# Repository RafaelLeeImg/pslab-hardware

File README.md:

# PSLab Hardware

This is a special branch `diff-img` where the changes made on all four layers relative to the immediate previous board is presented as a diff image.

## Current Layers

<details>
  <summary>External Layers</summary>

| Top | Bottom |
| --- | ------ |
|  |  |
</details>

<details>
  <summary>Internal Layers</summary>

| Power | Signal |
| ----- | ------ |
|  |  |
</details>

## Legend

🟥 what the new board has

🟦 what the previous board had

## Schematic Changes

## Board Changes

| Top Layer |
| ---------- |
|  |

| Bottom Layer |
| --------- |
|  |

| Power Layer |
| ---------- |
|  |

| Signal Layer |
| --------- |
|  |

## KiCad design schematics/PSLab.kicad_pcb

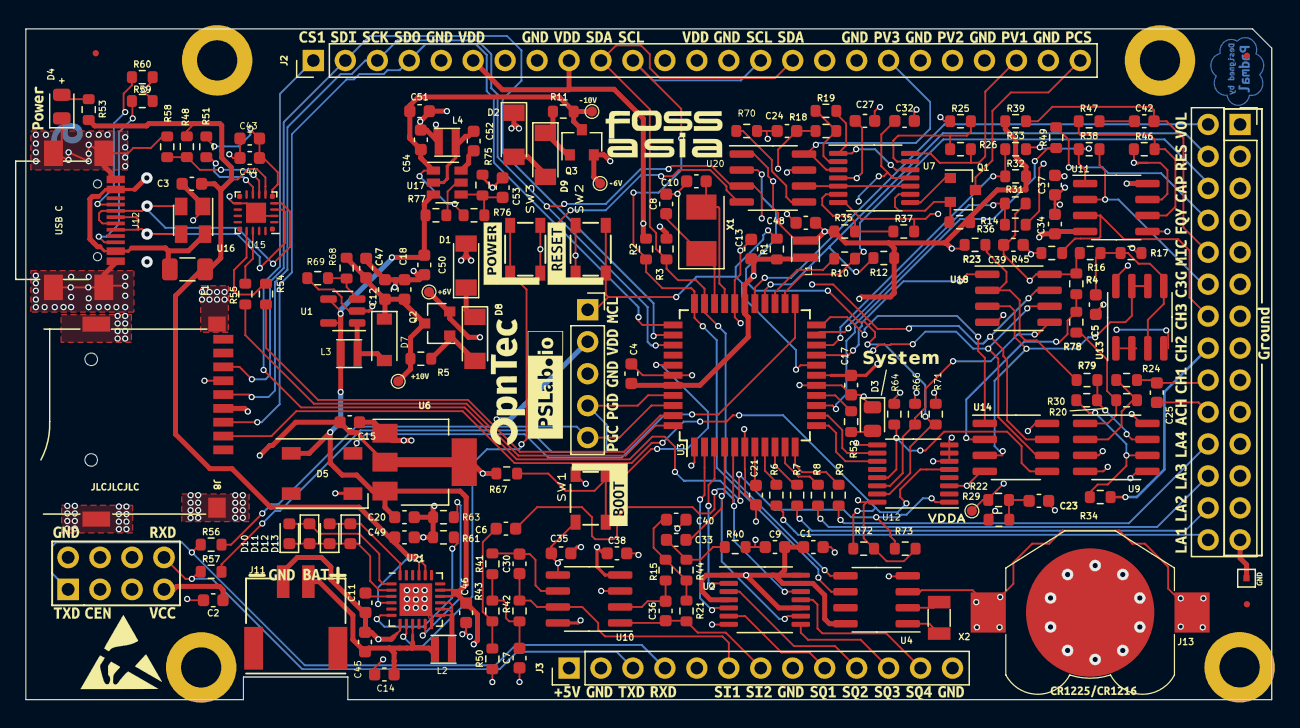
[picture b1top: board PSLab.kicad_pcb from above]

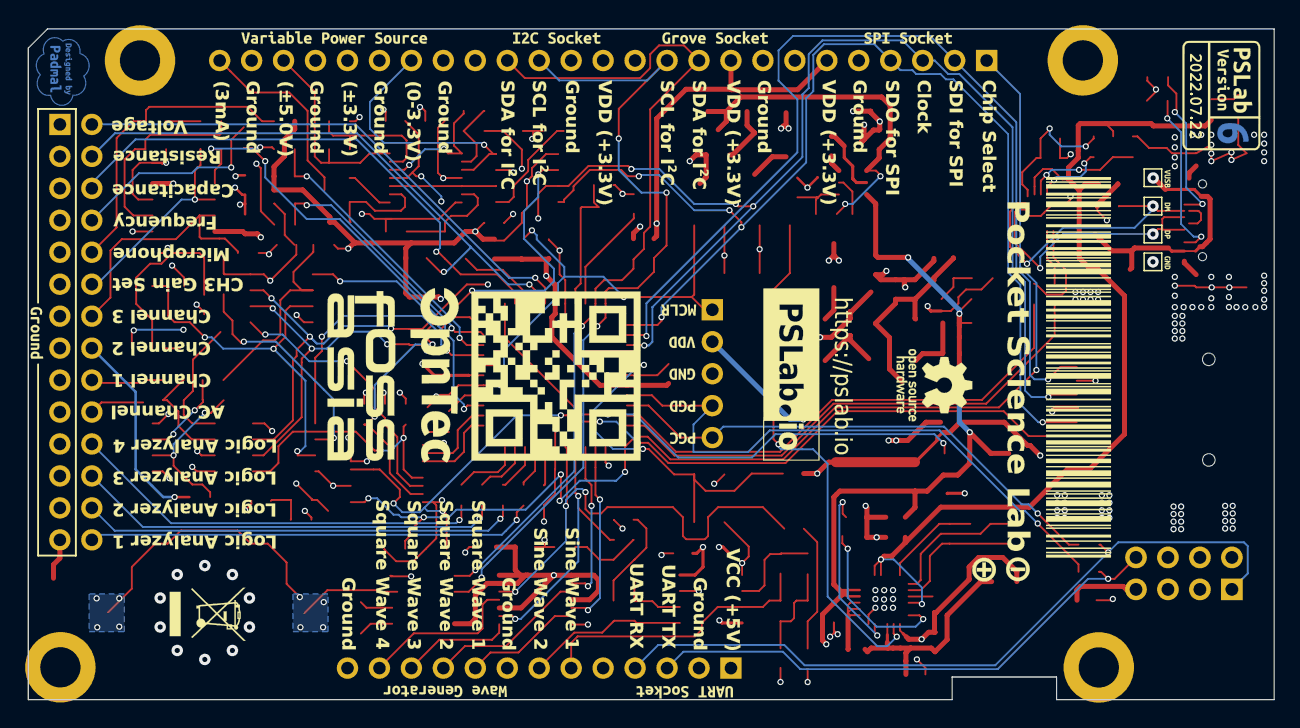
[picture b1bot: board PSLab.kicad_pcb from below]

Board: 4 copper layers, 99.0 x 53.3 mm, 195 parts (8 on the bottom side), 135 nets.

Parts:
C1, C2, C3, C4, C9, C13, C17, C18, C24, C25, C27, C32, C34, C35, C37, C38, C39, C43: 100nF; C_0603_1608Metric
C5, C7, C23, C40: 10nF; C_0603_1608Metric
C6, C12, C14, C15, C21, C33, C44: 10uF; C_0603_1608Metric
C8, C10, C53: 12pF; C_0603_1608Metric
C11: 2.2uF; C_0603_1608Metric
C20, C42, C52: 1uF; C_0603_1608Metric
C30, C36: 1nF; C_0603_1608Metric
C45, C46, C47, C48, C49, C50, C51, C54: 22uF; C_0603_1608Metric
D1, D2: 6.8V; D_MiniMELF
D3: GREEN; LED_0805_2012Metric
D4: BLUE; LED_0805_2012Metric
D5: WS2812B; LED_WS2812B_PLCC4_5.0x5.0mm_P3.2mm
D7: K1N5817HW-7-F; D_SOD-123
D8, D9: 1N4148W; D_MiniMELF
D10, D11, D12, D13: White; LED_0603_1608Metric
F1: 1A; Fuse_1206_3216Metric
FID1, FID2, FID3: Fiducial; Fiducial_0.5mm_Mask1.5mm
J1: DoublePins; PinSocket_2x14_P2.54mm_Vertical
J2: Conn_01x25; PinHeader_1x25_P2.54mm_Vertical
J3: Conn_01x13; PinHeader_1x13_P2.54mm_Vertical
J6: ESP01; ESP-01
J8: Micro_SD_Card_Det_9_pin; TF-015
J10: Programmer; PinSocket_1x05_P2.54mm_Vertical
J11: Battery_Cell; 2.0mm_connector_edge
J12: USB_C - Generic; USB_C_Receptacle_12pin_SMT
J13: CR1225; BatteryHolder_A359
L1, L3, L4: 3.3uH; L_Taiyo-Yuden_MD-2020
L2: 4.7uH; L_Taiyo-Yuden_MD-2020
MH1, MH2, MH3, MH4: M; MountingHole_3.2mm_M3_DIN965_Pad
Q1, Q3: MMBT3906; SOT-23
Q2: MMBT3904; SOT-23
R1, R4, R10, R14, R16, R17, R18, R19, R21, R23, R25, R29, R31, R32, R33, R35, R37, R38, R39, R42, R58, R64, R66, R67, R70, R71, R72, R73, R76, R78, R79: 10k; R_0603_1608Metric
R2, R3, R12, R15, R26, R41, R43, R44, R48, R52, R53, R59, R60: 5.1k; R_0603_1608Metric
R5, R11, R36, R47, R51: 1k; R_0603_1608Metric
R6, R7, R8, R9, R49: 200; R_0603_1608Metric
R20, R30, R40, R46, R50, R63, R77: 200k; R_0603_1608Metric
R22: 12k; R_0603_1608Metric
R24, R34, R45: 1M; R_0603_1608Metric
R54, R55, R56, R57: 18; R_0603_1608Metric
R61: 51k; R_0603_1608Metric
R68: 180k; R_0603_1608Metric
R69: 30k; R_0603_1608Metric
R75: 100k; R_0603_1608Metric
SW1, SW2, SW3: SW_MEC_5E; button_SPST_3x4x2.5
TP1, TP2, TP3, TP5, TP6: TEST; Test_Point_0.8mm
TP4, TP7: GND; TestPoint_Pad_1.0x1.0mm
TP8: VBUS; TestPoint_Pad_1.0x1.0mm
TP9: D-; TestPoint_Pad_1.0x1.0mm
TP10: D+; TestPoint_Pad_1.0x1.0mm
U1: AP3015A; SOT-23-5
U2: 74HC126; TSSOP-14_4.4x5mm_P0.65mm
U3: PIC24EP256GP204; TQFP-44_10x10mm_P0.8mm
U4: DS1307Z+T&R; SOIC-8_3.9x4.9mm_P1.27mm
U6: AMS1117-3.3; SOT-223-3_TabPin2
U7: LM324; TSSOP-14_4.4x5mm_P0.65mm
U9, U10, U11, U13: TL082; SOIC-8_3.9x4.9mm_P1.27mm
U12: 74HC4051; TSSOP-16_4.4x5mm_P0.65mm
U14, U18: MCP6S21-I/SN; SOIC-8_3.9x4.9mm_P1.27mm
U15: CP2102N-xxx-xQFN20x; QFN-20_EP_3x3_Pitch0.5mm
U16: SP0503BAHT; SOT-143
U17: MT1470; SOT-23-6
U20: MCP4822; SOIC-8_3.9x4.9mm_P1.27mm
U21: IP5189T; QFN-24-1EP_4x4mm_P0.5mm_EP2.6x2.6mm
X1: 12MHz; Crystal_SMD_5032-2Pin_5.0x3.2mm
X2: 32.768 kHz; Crystal_SMD_3215-2Pin_3.2x1.5mm
Z1: CR1225; Battery_CR1225
Z6: eWaste; WEEE-Logo_4.2x6mm_SilkScreen
Z7: PSLab BarCode; Barcode
Z8: QR Code; Website_QR
Z9: Val**; Silk
Z10: ESD-Logo; ESD-Logo_6.6x6mm_SilkScreen
Z11: OpenHardware; OSHW-Logo_5.7x6mm_SilkScreen

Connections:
+3V3: C2.1, C4.1, C13.1, C15.2, J2.6, J2.9, J2.13, J6.4 (CH_PD), J6.8 (VCC), J8.4 (VDD), J10.2, L1.2, R1.1, R2.2, R3.2, R64.2, R66.2, R67.2, R71.2, R72.2, R73.2, U3.28 (VDD), U3.40 (VDD), U6.2 (VO), U12.16 (VCC)
+5V: C1.1, C9.1, C20.2, C46.1, C50.1, D5.1 (VDD), J3.1, L3.1, R77.1, U1.4 (EN), U1.5 (VIN), U2.1, U2.4, U2.10, U2.13, U2.14 (VCC), U4.8 (VCC), U6.3 (VI), U17.3 (IN), U21.16 (VOUT), U21.17 (VOUT)
+6V: C27.1, C35.1, C37.1, Q2.2 (E), TP2.1, U7.4 (V+), U9.8 (V+), U10.8 (V+), U11.8 (V+), U13.8 (V+)
+9V: C12.1, C18.1, C47.1, D7.1 (K), Q2.3 (C), R5.2, R68.1, TP6.1
-6V: C32.1, C34.1, C38.1, Q3.2 (E), TP3.1, U7.11 (V-), U9.4 (V-), U10.4 (V-), U11.4 (V-), U13.4 (V-)
-9V: C51.2, C54.2, Q3.3 (C), R11.2, R76.2, TP5.1, U17.1 (GND)
/BAT+: C14.1, C45.1, J11.1 (+), L2.2, U21.9 (VBAT)
/CAP: J1.6, R10.2, U3.24 (PGED1|AN5|C1IN1-|RP35|RB3)
/CC1: J12.A5 (CC1), R60.2
/CC2: J12.B5 (CC2), R59.2
/CP2102_Vreg: C43.1, C44.1, R51.2, U15.6 (VDD)
/D+: J12.A6 (D+), J12.B6 (D+), TP10.1, U15.4 (D+), U16.3 (K)
/D-: J12.A7 (D-), J12.B7 (D-), TP9.1, U15.5 (D-), U16.2 (K)
/DAC.2: U7.5 (+), U7.10 (+), U20.6 (VB)
/LA1_: R6.2, U3.8 (RP42|RB10)
/LA2_: R7.2, U3.9 (RP43|RB11)
/LA3_: R8.2, U3.10 (RPI44|RB12)
/LA4_: R9.2, U3.11 (RPI45|CTPLS|RB13)
/LD1: D12.2 (A), D13.1 (K), U21.24 (L1)
/LD2: D10.2 (A), D11.1 (K), U21.1 (L2)
/LD3: D10.1 (K), D11.2 (A), D12.1 (K), D13.2 (A), U21.2 (L3)
/OSC_IN: C10.1, U3.30 (OSC1|CLKI|RA2), X1.2
/OSC_OUT: C8.1, U3.31 (OSC2|CLKO|RA3), X1.1
/OSC_REF1: U13.6 (-), U13.7, U14.3 (VREF), U18.3 (VREF)
/OSC_REF2: C23.1, R22.1, R29.1
/RES: J1.4, R12.1, U3.26 (AN7|C3IN1-|C4IN1-|RC1)
/RxD: R54.2, U3.43 (RP39|INT0|RB7)
/SQR1_: U2.5, U3.2 (RP54|RC6)
/SQR2_: U2.2, U3.3 (RP55|RC7)
/TxD: R55.2, U3.44 (TCK|ASCL1|RP40|T4CK|RB8)
/VBusSense: R48.2, R58.2, U15.8 (VBUS)
/VINPUT: C3.2, C49.1, F1.2, R48.1, R53.1, U15.7 (VregIn), U21.4 (VTHS), U21.20 (VIN), U21.21 (VIN)
/VOL: J1.2, U3.27 (AN8|C3IN1+|RC2)
/VUSBIN: F1.1, J12.A4 (VBUS), J12.A9 (VBUS), J12.B4 (VBUS), J12.B9 (VBUS), TP8.1, U16.4 (K)
ACH1: C25.2, J1.20
BOOT: R67.1, SW1.1, SW1.2, U3.38 (SCL1|RPI53|RC5)
CH1: C25.1, J1.18, R24.2
CH1_IN: U3.22 (PGEC3|AN3|OA1OUT|RPI33|RB1), U14.1 (OUT)
CH2: J1.16, R34.1
CH2_IN: U3.19 (AN0|OA2OUT|RA0), U18.1 (OUT)
CH3: J1.14, R45.2, U11.3 (+)
CH3.GAIN: J1.12, R38.1, U11.2 (-)
CH3_IN: R32.1, R33.1, U3.20 (AN1|C2IN1+|RA1)
CS1: R64.1, U12.13 (A0), U14.5 (CS)
CS2: R66.1, U12.14 (A1), U18.5 (CS)
CS3: R71.1, U12.15 (A2), U20.2 (~CS)
CS.CH1: U3.12 (TDO|RA10), U12.11 (S0)
CS.CH2: U3.13 (TDI|RA7), U12.10 (S1)
CS.CH3: U3.1 (TMS|ASDA1|RP41|RB9), U12.9 (S2)
FQy: J1.8, R49.2
GND: C1.2, C2.2, C3.1, C4.2, C5.2, C7.2, C8.2, C9.2, C10.2, C11.2, C12.2, C13.2, C14.2, C15.1, C17.2, C18.2, C20.1, C21.2, C23.2, C24.1, C27.2, C32.2, C34.2, C35.2, C37.2, C38.2, C39.2, C40.2, C43.2, C44.2, C45.2, C46.2, C47.2, C48.2, C49.2, C50.2, C51.1, C53.1, C54.1, D1.2 (A), D2.1 (K), D3.1 (K), D4.1 (K), D5.3 (VSS), J1.1, J1.3, J1.5, J1.7, J1.9, J1.11, J1.13, J1.15, J1.17, J1.19, J1.21, J1.23, J1.25, J1.27, J2.5, J2.8, J2.14, J2.18, J2.20, J2.22, J2.24, J3.2, J3.8, J3.13, J6.1 (GND), J8.6 (VSS), J8.10 (SHIELD), J10.3, J11.2 (-), J12.A1 (GND), J12.A12 (GND), J12.B1 (GND), J12.B12 (GND), J12.S1 (SHIELD), J13.2 (-), L4.2, MH1.1, MH2.1, MH3.1, MH4.1, R17.2, R25.1, R29.2, R40.1, R45.1, R50.1, R58.1, R59.1, R60.1, R61.2, R63.2, R69.2, R70.1, R75.1, SW1.3 (K), SW1.4 (A), SW2.3 (K), SW2.4 (A), SW3.1, SW3.2, TP4.1, TP7.1, U1.2 (GND), U2.7 (GND), U3.6 (VSS), U3.16 (GND), U3.29 (VSS), U3.39 (VSS), U4.4 (GND), U6.1 (GND), U9.3 (+), U9.5 (+), U10.3 (+), U10.5 (+), U11.5 (+), U12.3 (A), U12.6 (~E), U12.7 (VEE), U12.8 (GND), U14.4 (GND), U15.3 (GND), U15.12 (GND), U15.21 (GND), U16.1 (A), U18.4 (GND), U20.7 (Vss), U21.7 (AGND), U21.12 (PGND), U21.25 (GND)
LA1: J1.28, R6.1
LA2: J1.26, R7.1
LA3: J1.24, R8.1
LA4: J1.22, R9.1
MCLR: J10.1, R1.2, SW2.1, SW2.2, U3.18 (~MCLR)
MIC: C42.2, J1.10, R39.1
MIC_IN: R14.1, R31.2, U3.21 (PGED3|AN2|C2IN1-|RPI32|RB0)
unnamed: C5.1, R16.1, R17.1, U13.3 (+), U13.5 (+)
unnamed: C6.2, R43.1, R50.2
unnamed: C7.1, R41.1, R42.1, R43.2
unnamed: C11.1, U21.3 (VDD)
unnamed: C21.1, U3.7 (VCAP)
unnamed: C30.2, R41.2, U10.6 (-)
unnamed: C33.2, R40.2, R44.2
unnamed: C36.2, R15.2, U10.2 (-)
unnamed: C40.1, R15.1, R21.1, R44.1
unnamed: C42.1, R47.1
unnamed: C52.1, L4.1, U17.2 (SW)
unnamed: C52.2, U17.6 (BST)
unnamed: C53.2, R75.2, R76.1, U17.4 (FB)
unnamed: D1.1 (K), D8.1 (K)
unnamed: D2.2 (A), D9.2 (A)
unnamed: D3.2 (A), R52.2
unnamed: D4.2 (A), R53.2
unnamed: D7.2 (A), L3.2, U1.1 (SW)
unnamed: D8.2 (A), Q2.1 (B), R5.1
unnamed: D9.1 (K), Q3.1 (B), R11.1
unnamed: J13.1 (+), U4.3 (VBAT)
unnamed: L2.1, U21.13 (LX), U21.14 (LX), U21.15 (LX)
unnamed: Q1.1 (B), U7.8
unnamed: Q1.2 (E), R36.1, U7.9 (-)
unnamed: R4.2, R78.2, U14.2 (CHA)
unnamed: R10.1, U3.25 (AN6|OA3OUT|C4IN1+|RC0)
unnamed: R14.2, R46.2, U11.7
unnamed: R18.2, R19.2, U7.2 (-)
unnamed: R19.1, U7.1, U7.12 (+)
unnamed: R20.1, R24.1, U9.2 (-)
unnamed: R20.2, R78.1, U9.1
unnamed: R23.2, R79.2, U18.2 (CHA)
unnamed: R25.2, R26.2, U7.13 (-)
unnamed: R30.1, R79.1, U9.7
unnamed: R30.2, R34.2, U9.6 (-)
unnamed: R33.2, R38.2, U11.1
unnamed: R35.2, R37.1, U7.6 (-)
unnamed: R46.1, R47.2, U11.6 (-)
unnamed: R49.1, U3.14 (RPI46|T3CK|RB14)
unnamed: R51.1, U15.9 (RSTb)
unnamed: R54.1, U15.17 (RXD)
unnamed: R55.1, U15.18 (TXD)
unnamed: R61.1, U21.6 (NTC)
unnamed: R63.1, U21.11 (ICHG)
unnamed: R68.2, R69.1, U1.3 (FB)
unnamed: R70.2, U20.5 (~LDAC)
unnamed: R77.2, U17.5 (EN)
unnamed: SW3.3 (K), SW3.4 (A), U21.8 (KEY)
unnamed: U4.1 (X1), X2.1
unnamed: U4.2 (X2), X2.2
unnamed: U13.1, U13.2 (-)
PCS: J2.25, Q1.3 (C)
PGC2: J10.5, R56.1, U3.42 (PGEC2|ASCL2|RP38|RB6)
PGD2: J10.4, R57.1, U3.41 (PGED2|ASDA2|RP37|RB5)
PVS1: J2.23, R26.1, U7.14
PVS2: J2.21, R37.2, U7.7
PVS3: J2.19, U7.3 (+), U20.8 (VA)
RGB: D5.4 (DIN), U3.23 (PGEC1|AN4|C1IN1+|RPI34|RB2)
RxD2: J3.4, J6.2 (TXD), R56.2
SCK: J2.3, J8.5 (CLK), U3.36 (SCK1|RPI51|RC3), U14.7 (SCK), U18.7 (SCK), U20.3 (SCK)
SCL: J2.11, J2.15, R2.1, U3.33 (SCL2|RP36|RB4), U4.6 (SCL)
SD.CS: J8.2 (DAT3/CD), R72.1, U12.5 (A5)
SDA: J2.10, J2.16, R3.1, U3.32 (SDA2|RPI24|RA8), U4.5 (SDA)
SDI: J2.2, J8.7 (DAT0), U3.35 (SDI1|RPI25|RA9)
SDO: J2.4, J8.3 (CMD), U3.34 (SDO1|RP20|T1CK|RA4), U14.6 (SDI), U18.6 (SDI), U20.4 (SDI)
SINE1: C30.1, J3.6, R42.2, U10.7
SINE2: C36.1, J3.7, R21.2, U10.1
SPI.CS: J2.1, R73.1, U12.1 (A4)
SQR1: J3.9, U2.6
SQR2: J3.10, U2.3
SQR3: J3.11, U2.8
SQR3_: C33.1, U2.9, U3.4 (RP56|RC8)
SQR4: J3.12, U2.11
SQR4_: C6.1, U2.12, U3.5 (RP57|RC9)
STAT: R52.1, U3.15 (RPI47|T5CK|RB15)
TxD2: J3.3, J6.7 (RXD), R57.2
VDDA: C17.1, C24.2, C39.1, C48.1, L1.1, R4.1, R12.2, R16.2, R18.1, R22.2, R23.1, R31.1, R32.2, R35.1, R36.2, R39.2, TP1.1, U3.17 (AVDD), U14.8 (VDD), U18.8 (VDD), U20.1 (Vdd)

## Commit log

2021-10-20 chore: updating board diff images
2021-12-13 chore: modify oscilloscope reference voltage divider resister from 5% to 1%
2021-12-13 refactor: modify LDFM33 to HT7333-A
2021-12-13 chore: add FP6192 in PSLab.lib
2021-12-13 refactor: modify TC1240A to FP6291
2021-12-13 chore: add TP7660H
2021-12-13 refactor: modify TC7660 to TP7660H
2021-12-14 chore: add PL2303 and IP5189T
2021-12-14 refactor: replace LTC4040 with IP5189T
2021-12-14 Temp
2021-12-14 Temp2
2021-12-14 Temp3
2021-12-15 Temp4
2021-12-15 Temp5
2021-12-15 chore: add footprint QFN20-3mmx3mm
2021-12-16 Temp6
2021-12-16 chore: replace switch to SPST_3x4x2.5
2021-12-16 refactor: fix all warnings, replace SW1 and SW2, before gerber generation
2021-12-16 chore: generated gerber
2021-12-20 Temp7
2021-12-22 Add battery socket, add SW3
2021-12-22 Add battery socket and SW3 in PCB
2021-12-22 refactor: replace PGA MAX6S@! with TL082 and MAX5400
2021-12-22 refactor: replace PGA MAX6S@! with TL082 and MAX5400, modify PCB
2021-12-22 refactor: replace MCP4728 with 2 MPC4822
2021-12-22 Temp8
2021-12-22 chore: update button footprint
2021-12-22 refactor: update PCB
2021-12-22 Before Send to manufacturer
2021-12-23 chore: add pull-up resistors to SPI_CS SD_CS pins
2021-12-23 chore: update silk of PSLab
2021-12-23 chore: update PCB
2021-12-23 Remove all 100uF capcitors
2021-12-23 chore: Delete 100uF capacitors
2021-12-23 Temp9
2021-12-24 chore: add IP5219
2021-12-24 refactor: replace IP5189T to IP5219T
2021-12-24 chore: add IP5219, to squash
2021-12-24 chore: generate gerber and drill files
2021-12-31 chore: modify 0.1uF to 100nF
2022-02-16 chore: add footprints
2022-02-16 chore: add tf card schematic symbol with detect
2022-02-16 chore: modify tf card slot
2022-02-16 chore: update tf card footprint
2022-02-16 chore: update project files
2022-02-16 chore: update gerber files
2022-02-16 refactor: replace IP5219 to IP51289T
2022-02-16 refactor: replace IP5219 to IP51289T in PCB
2022-02-16 chore: update gerber
2022-03-17 20220302, send to manufacturer
2022-03-17 refactor: generate negative voltage using a buck converter
2022-04-16 Update to kicad6
2022-06-08 20220608
2022-07-21 chore: remove 7660
2022-07-21 For 2022 June
2022-09-02 refactor: send to manufacturer
2022-09-03 refactor: update to kicad v6 and generate negative voltage using a buck converter
2022-09-03 chore: modify descriptions and silk screens
2023-02-10 added custom mounting holes so that DRC errors vanish
2023-05-06 chore: modify text status to system of LED
2023-05-06 chore: update silk screen
2023-05-06 chore: move edge connector inner
2023-05-06 chore: modify battery silk screen
